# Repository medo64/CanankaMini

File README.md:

[Cananka Mini](https://medo64.com/cananka/)
===========================================

Cananka Mini is a minimalistic device connecting to CAN bus using USB serial
port (SLCAN compatible). It has USB type-A connector on computer side and 3.81
mm strip headers on CAN bus side.

The following hardware version are also available:
* [Full](https://github.com/medo64/Cananka) (isolated and in the case)
* [Framework Expansion Card](https://github.com/medo64/CanankaFEC) (non-isolated, in framework expansion card format)
* [HAT](https://github.com/medo64/CanankaHAT) (intended for Raspberry Pi)

The following additional repositories might be of interest:
* [Firmware](https://github.com/medo64/Cananka.Firmware)
* [Protocol](https://github.com/medo64/Cananka.Firmware/blob/main/PROTOCOL.md)
* [Test software](https://github.com/medo64/Cananka.Software)

---

*You can check my blog and other projects at [www.medo64.com](https://medo64.com/cananka/mini/)*

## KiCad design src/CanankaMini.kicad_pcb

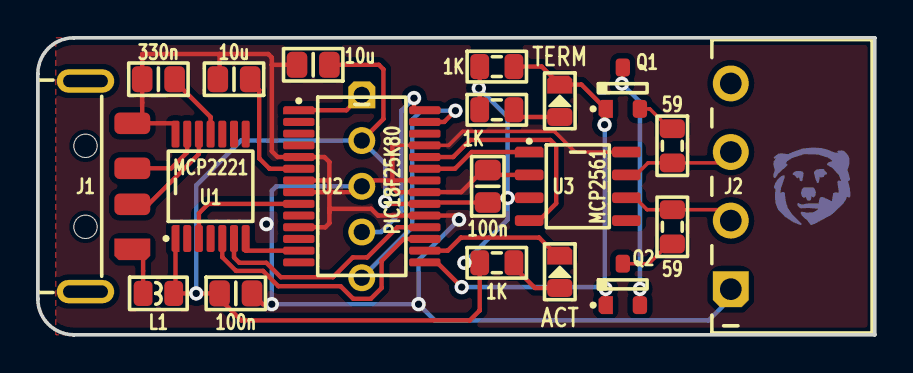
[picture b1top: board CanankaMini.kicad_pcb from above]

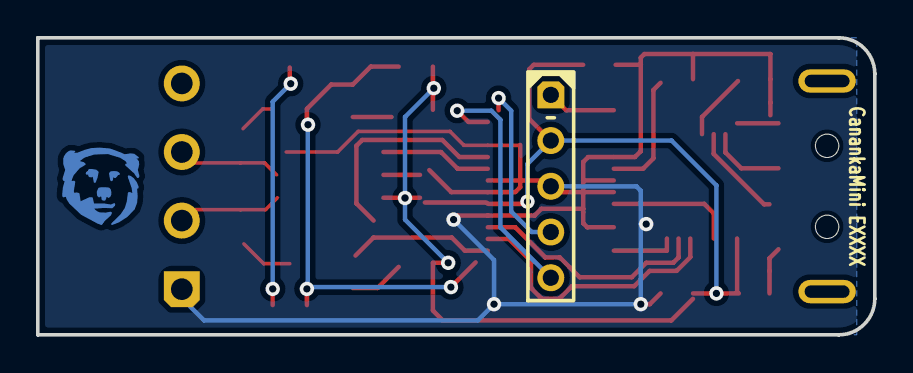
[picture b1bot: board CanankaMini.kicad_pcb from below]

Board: 2 copper layers, 46.5 x 16.5 mm, 22 parts (2 on the bottom side), 25 nets.

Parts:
C1, C2: 100n; C (0805)
C3: 330n; C (0805)
C4, C5: 10u; C (0805)
DS1: ACT; DS (0805)
DS2: TERM; DS (0805)
ICON: Medo64; ICON Medo64
ICSP: Microchip PIC; ICSP PIC Pogo SS (5w)
J1: 48037-2200; J USB A 2.0 Plug (4w)
J2: MC 1,5/4; J Phoenix MC [CAN] (4w)
L1: 40R; L Ferrite (0805)
Q1, Q2: DMP3056L-7; Q MOSFET-P (SOT23-3)
R1, R2: 59; R (0805)
R3, R4, R5: 1K; R (0805)
U1: MCP2221; U Transceiver UART+I2C [MCP2221] (TSSOP-14)
U2: PIC18F25K80; U Micro [PIC18F25K80] (SSOP-28)
U3: MCP2561; U Transceiver CAN [MCP2561] (SOIC-8)

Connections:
5V: C1.1, C2.1, C5.1, ICSP.2, L1.2, R3.1, R4.1, R5.1, U1.1, U2.20, U3.3
CAN_H: J2.3, R1.2, U3.7
CAN_H_TERM: Q1.2, R1.1
CAN_I_TERM: Q1.3, Q2.2
CAN_L: J2.2, R2.2, U3.6
CAN_L_TERM: Q2.3, R2.1
CAN_RX: U2.24, U3.4
CAN_TX: U2.23, U3.1
GND: C1.2, C2.2, C3.2, C4.2, C5.2, ICSP.3, J1.4, J2.1, U1.14, U2.5, U2.7, U2.8, U2.11, U2.19, U2.21, U2.22, U2.25, U3.2, U3.8
ICSP_PGC: ICSP.5, U2.27
ICSP_PGD: ICSP.4, U2.28
ICSP_VPP: ICSP.1, U2.1
IO_CONTROL_TERMINATE#: DS2.1, Q1.1, Q2.1, R5.2, U2.15
IO_LED_ACTIVITY#: DS1.1, U2.16
IO_USBCFG: U1.7, U2.13
LED_ACTIVITY: DS1.2, R3.2
LED_CAN_TERMINATE: DS2.2, R4.2
OSC: U1.3, U2.9
UART_RX: U1.6, U2.18
UART_TX: U1.5, U2.17
USB_5V: J1.1, L1.1
USB_DM: J1.2, U1.12
USB_DP: J1.3, U1.13
V_CORE: C4.1, U2.6
V_USB: C3.1, U1.11

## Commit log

2024-06-04 Initial version seeded from the main Cananka repository
2024-06-04 Initial KiCAD version
2024-06-05 Added current limiting
2024-06-05 Adjusted current limiting
2024-06-05 Fixing up component list
2024-06-06 Moved designators a bit
2024-06-06 Updated flood fill
2024-09-03 Removing power-on circuit
2024-09-06 Fixing termination circuit
2024-09-06 Swapped mosfet for a more resilient one
2024-09-06 Moved config file
2024-09-08 Fixing termination MOSFET connections
